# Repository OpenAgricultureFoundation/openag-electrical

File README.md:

# OpenAg Body
Body of electrical hardware to go with the brain software.
Electrical design based in Eagle. Mechanical design based in Solidworks.

*WORK IN PROGRESS*

## Electrical Design
### Setup
- Clone openag-body repo
- Point eagle program directories at corresponding openag-body repo

### Projects
- Create project directory structure
- Follow naming conventions
- Use standard docframe
- Add design blocks on standard grid
- Connect design blocks

### Parts
- Create part in logical group
- Follow naming conventions
- Add description using Digikey scraper
- Add required attributes
- Add standard name, value, & orientation

### Design Blocks
- Build on standard grid
- Add standard artwork
- Add standard signal interface
- Follow naming conventions

### Manufacturing Files
- Run CAM processor job
- Run BOM generation script

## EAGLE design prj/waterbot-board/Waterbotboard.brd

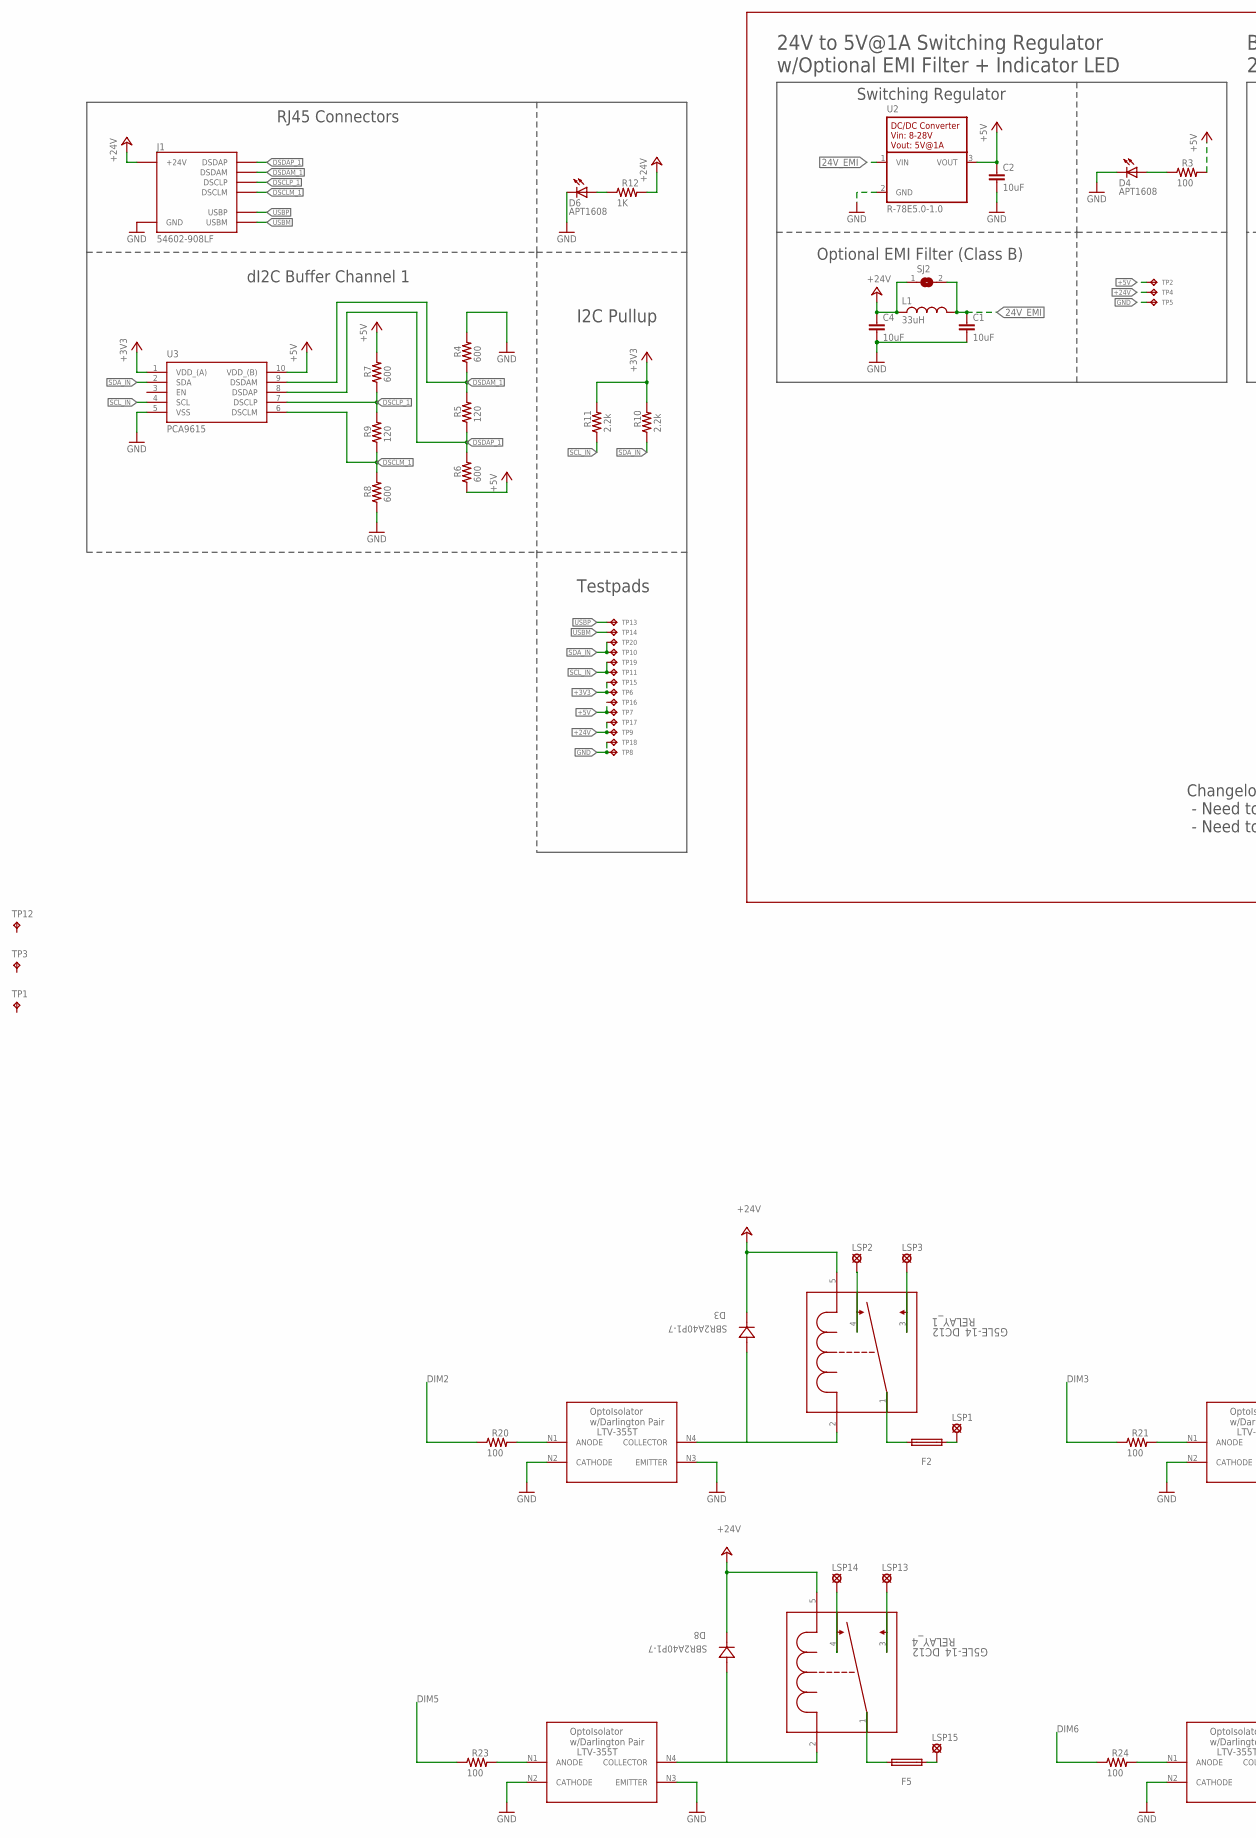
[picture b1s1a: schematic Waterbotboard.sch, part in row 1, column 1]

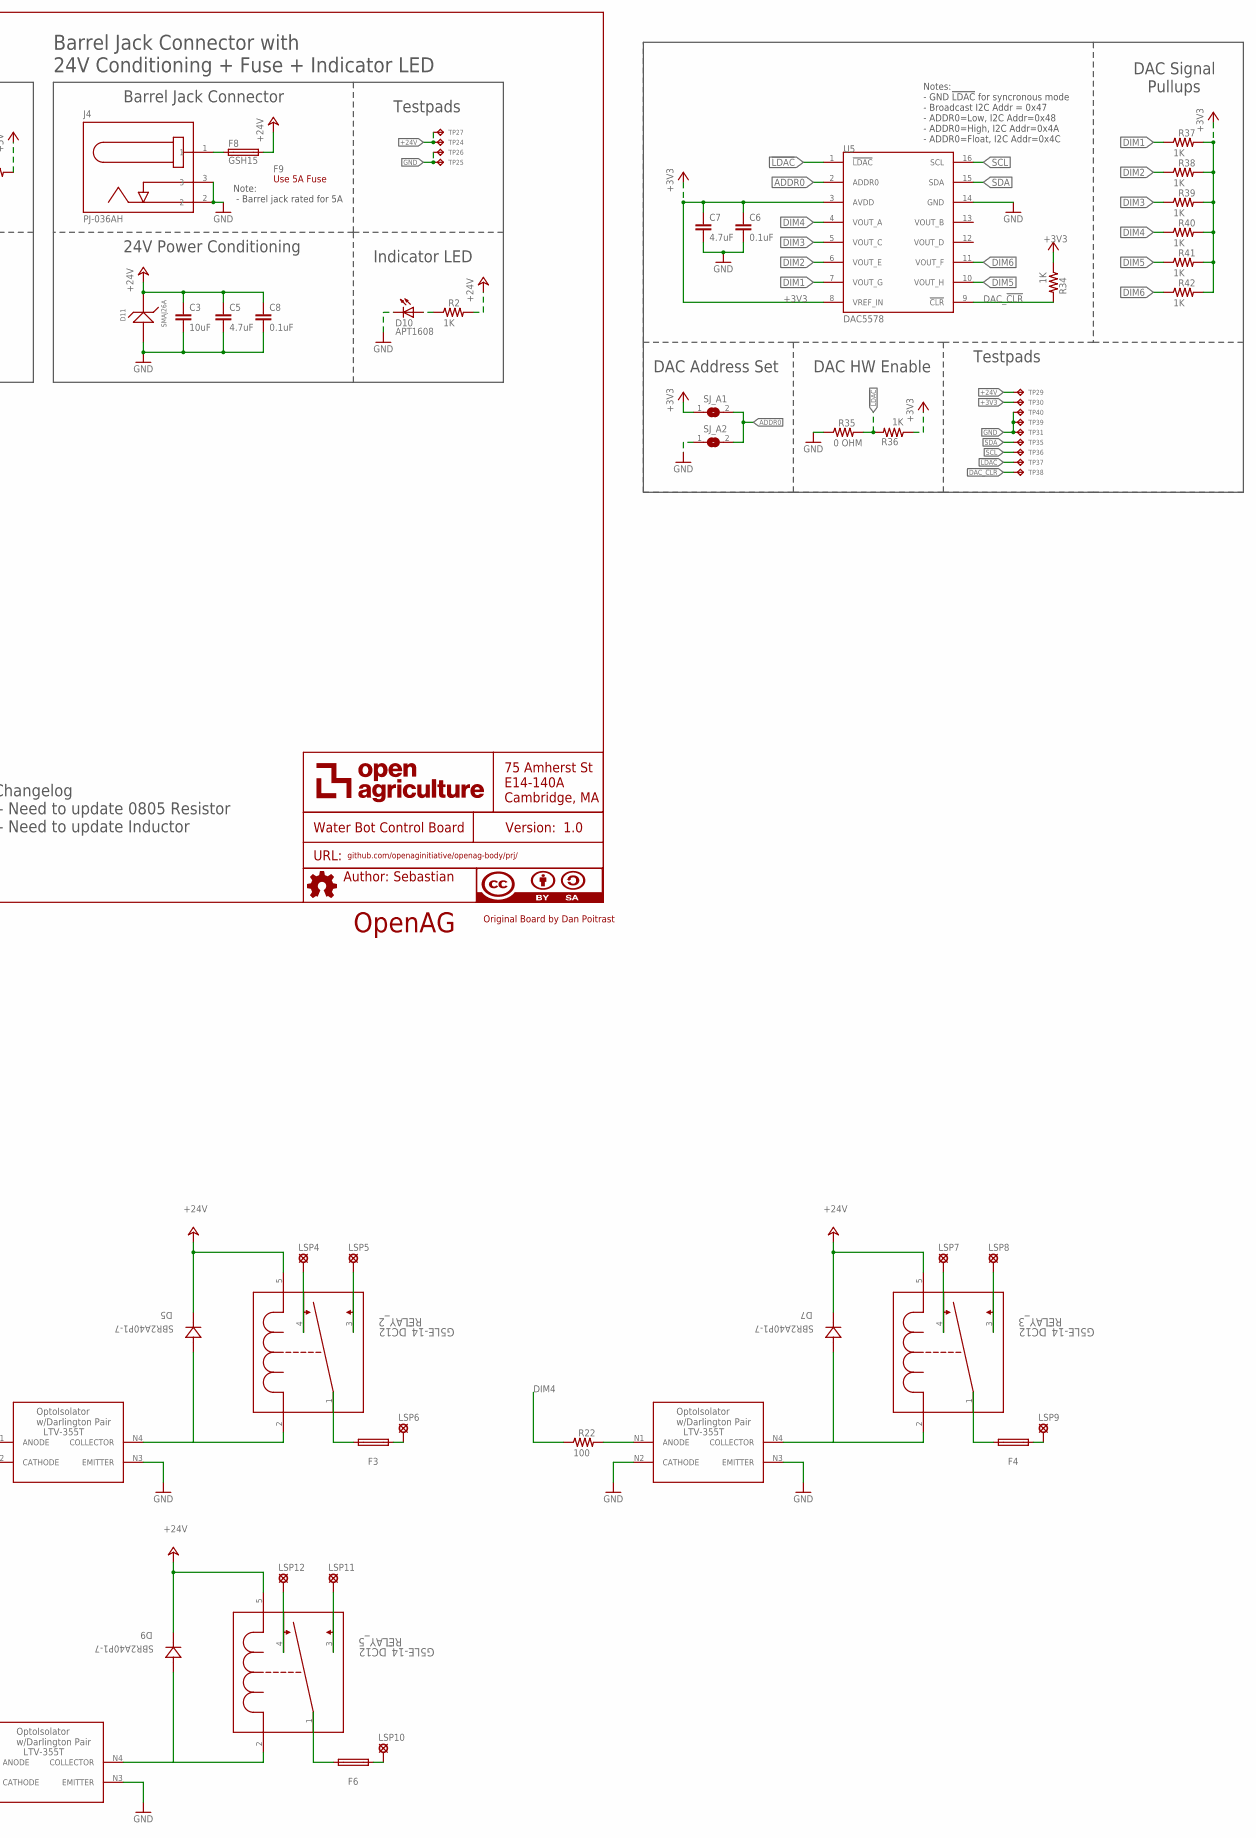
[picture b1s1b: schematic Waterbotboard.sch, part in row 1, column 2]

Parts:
C1, C2, C3, C4: 10uF; C0805
C5, C7: 4.7uF; C0805
C6, C8: 0.1uF; C0603
D3, D5, D7, D8, D9: SBR2A40P1-7; POWERDI123
D4, D6, D10: APT1608; CHIPLED_0603
D11: SMAJ26A; SMA
F2, F3, F4, F5, F6, F8: GSH15
F9: Use 5A Fuse; FUSE-CARTRIDGE
J1: 54602-908LF; RJ45-DI2C-USB-54602-908LF
J4: PJ-036AH; BARREL-JACK-PJ-036AH
L1: 33uH; 29333C
LSP1, LSP2, LSP3, LSP4, LSP5, LSP6, LSP7, LSP8, LSP9, LSP10, LSP11, LSP12, LSP13, LSP14, LSP15: LSP13
R2, R12, R34, R36, R37, R38, R39, R40, R41, R42: 1K; RC0603N
R3, R20, R21, R22, R23, R24: 100; RC0603N
R4, R6, R7, R8: 600; RC0603N
R5, R9: 120; RC0603N
R10, R11: 2.2k; RC0603N
R35: 0 OHM; RC0603N
RELAY_1, RELAY_2, RELAY_3, RELAY_4, RELAY_5: G5LE-14_DC12; RELAY_G5LE-1
SJ2: EMI-BYPASS
SJ_A1, SJ_A2: SOLDERJUMPERREFLOW_NOPASTE; SJ1
TP1, TP3, TP12: TPB2,54; B2,54
TP2, TP4, TP5: TPTP06R; TP06R
TP6, TP7, TP8, TP9, TP10, TP11, TP13, TP14, TP15, TP16, TP17, TP18, TP19, TP20, TP24, TP25, TP26, TP27, TP29, TP30, TP31, TP35, TP36, TP37, TP38, TP39, TP40: TPTP04R; TP04R
U2: R-78E5.0-1.0
U3: PCA9615; SOP50P490X110-10N
U5: DAC5578; TSSOP16
U$6: AUTHOR
U$7: TITLE
U$10, U$11, U$12, U$13, U$14: LTV-355T

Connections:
24V_EMI: C1.1, L1.2, SJ2.2, U2.1 (VIN)
24V_IN1: F8.1, J4.1
!LDAC!: R35.2, R36.2, TP37.1, U5.1 (!LDAC!)
+3V3: C6.1, C7.1, R10.2, R11.2, R34.1, R36.1, R37.2, R38.2, R39.2, R40.2, R41.2, R42.2, SJ_A1.1, TP6.1, TP15.1, TP30.1, U3.1 (VDD_(A)), U5.3 (AVDD), U5.8 (VREF_IN)
+5V: C2.1, R3.2, R6.1, R7.2, TP2.TP, TP7.1, TP16.1, U2.3 (VOUT), U3.10 (VDD_(B))
+24V: C3.1, C4.1, C5.1, C8.1, D3.-, D5.-, D7.-, D8.-, D9.-, D11.1, F8.2, J1.24V(6) (+24V), L1.1, R2.2, R12.2, RELAY_1.5, RELAY_2.5, RELAY_3.5, RELAY_4.5, RELAY_5.5, SJ2.1, TP4.TP, TP9.1, TP17.1, TP24.1, TP27.1, TP29.1
ADDR0: SJ_A1.2, SJ_A2.2, U5.2 (ADDR0)
DAC_!CLR!: R34.2, TP38.1, U5.9 (!CLR!)
DIM1: R37.1, U5.7 (VOUT_G)
DIM2: R20.1, R38.1, U5.6 (VOUT_E)
DIM3: R21.1, R39.1, U5.5 (VOUT_C)
DIM4: R22.1, R40.1, U5.4 (VOUT_A)
DIM5: R23.1, R41.1, U5.10 (VOUT_H)
DIM6: R24.1, R42.1, U5.11 (VOUT_F)
DSCLM_1: J1.DSCLM(5) (DSCLM), R8.2, R9.1, U3.6 (DSCLM)
DSCLP_1: J1.DSCLP(4) (DSCLP), R7.1, R9.2, U3.7 (DSCLP)
DSDAM_1: J1.DSDAM(2) (DSDAM), R4.1, R5.2, U3.9 (DSDAM)
DSDAP_1: J1.DSDAP(1) (DSDAP), R5.1, R6.2, U3.8 (DSDAP)
GND: C1.2, C2.2, C3.2, C4.2, C5.2, C6.2, C7.2, C8.2, D4.C, D6.C, D10.C, D11.2, J1.GND(3) (GND), J4.2, J4.3, R4.2, R8.1, R35.1, SJ_A2.1, TP5.TP, TP8.1, TP18.1, TP25.1, TP26.1, TP31.1, TP39.1, TP40.1, U2.2 (GND), U3.5 (VSS), U5.14 (GND), U$10.N2 (CATHODE), U$10.N3 (EMITTER), U$11.N2 (CATHODE), U$11.N3 (EMITTER), U$12.N2 (CATHODE), U$12.N3 (EMITTER), U$13.N2 (CATHODE), U$13.N3 (EMITTER), U$14.N2 (CATHODE), U$14.N3 (EMITTER)
unnamed: F2.1, LSP1.MP
unnamed: F5.1, LSP15.MP
unnamed: F6.1, LSP10.MP
unnamed: F3.1, LSP6.MP
unnamed: F4.1, LSP9.MP
unnamed: LSP2.MP, RELAY_1.4
unnamed: LSP4.MP, RELAY_2.4
unnamed: LSP7.MP, RELAY_3.4
unnamed: D4.A, R3.1
unnamed: D3.+, RELAY_1.2 (1), U$10.N4 (COLLECTOR)
unnamed: D6.A, R12.1
unnamed: F2.2, RELAY_1.1 (2)
unnamed: LSP3.MP, RELAY_1.3
unnamed: LSP12.MP, RELAY_5.4
unnamed: R20.2, U$10.N1 (ANODE)
unnamed: D5.+, RELAY_2.2 (1), U$11.N4 (COLLECTOR)
unnamed: F3.2, RELAY_2.1 (2)
unnamed: LSP5.MP, RELAY_2.3
unnamed: LSP14.MP, RELAY_4.4
unnamed: R21.2, U$11.N1 (ANODE)
unnamed: D7.+, RELAY_3.2 (1), U$12.N4 (COLLECTOR)
unnamed: F4.2, RELAY_3.1 (2)
unnamed: LSP8.MP, RELAY_3.3
unnamed: R22.2, U$12.N1 (ANODE)
unnamed: D8.+, RELAY_4.2 (1), U$13.N4 (COLLECTOR)
unnamed: F5.2, RELAY_4.1 (2)
unnamed: LSP13.MP, RELAY_4.3
unnamed: D10.A, R2.1
unnamed: R23.2, U$13.N1 (ANODE)
unnamed: D9.+, RELAY_5.2 (1), U$14.N4 (COLLECTOR)
unnamed: F6.2, RELAY_5.1 (2)
unnamed: LSP11.MP, RELAY_5.3
unnamed: R24.2, U$14.N1 (ANODE)
SCL: TP36.1, U5.16 (SCL)
SCL_IN: R11.1, TP11.1, TP19.1, U3.4 (SCL)
SDA: TP35.1, U5.15 (SDA)
SDA_IN: R10.1, TP10.1, TP20.1, U3.2 (SDA)
USBM: J1.USBM(8) (USBM), TP14.1
USBP: J1.USBP(7) (USBP), TP13.1

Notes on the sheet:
Changelog - Need to update 0805 Resistor - Need to update Inductor
OpenAG
Original Board by Dan Poitrast
24V to 5V@1A Switching Regulator w/Optional EMI Filter + Indicator LED
Switching Regulator
Optional EMI Filter (Class B)
dI2C Buffer Channel 1
RJ45 Connectors
Testpads
I2C Pullup
LTV-355T
Notes: - GND !LDAC! for syncronous mode - Broadcast I2C Addr = 0x47 - ADDR0=Low, I2C Addr=0x48 - ADDR0=High, I2C Addr=0x4A - ADDR0=Float, I2C Addr=0x4C
DAC Signal Pullups
DAC Address Set
DAC HW Enable
Barrel Jack Connector
Barrel Jack Connector with 24V Conditioning + Fuse + Indicator LED
24V Power Conditioning
Indicator LED
Note: - Barrel jack rated for 5A

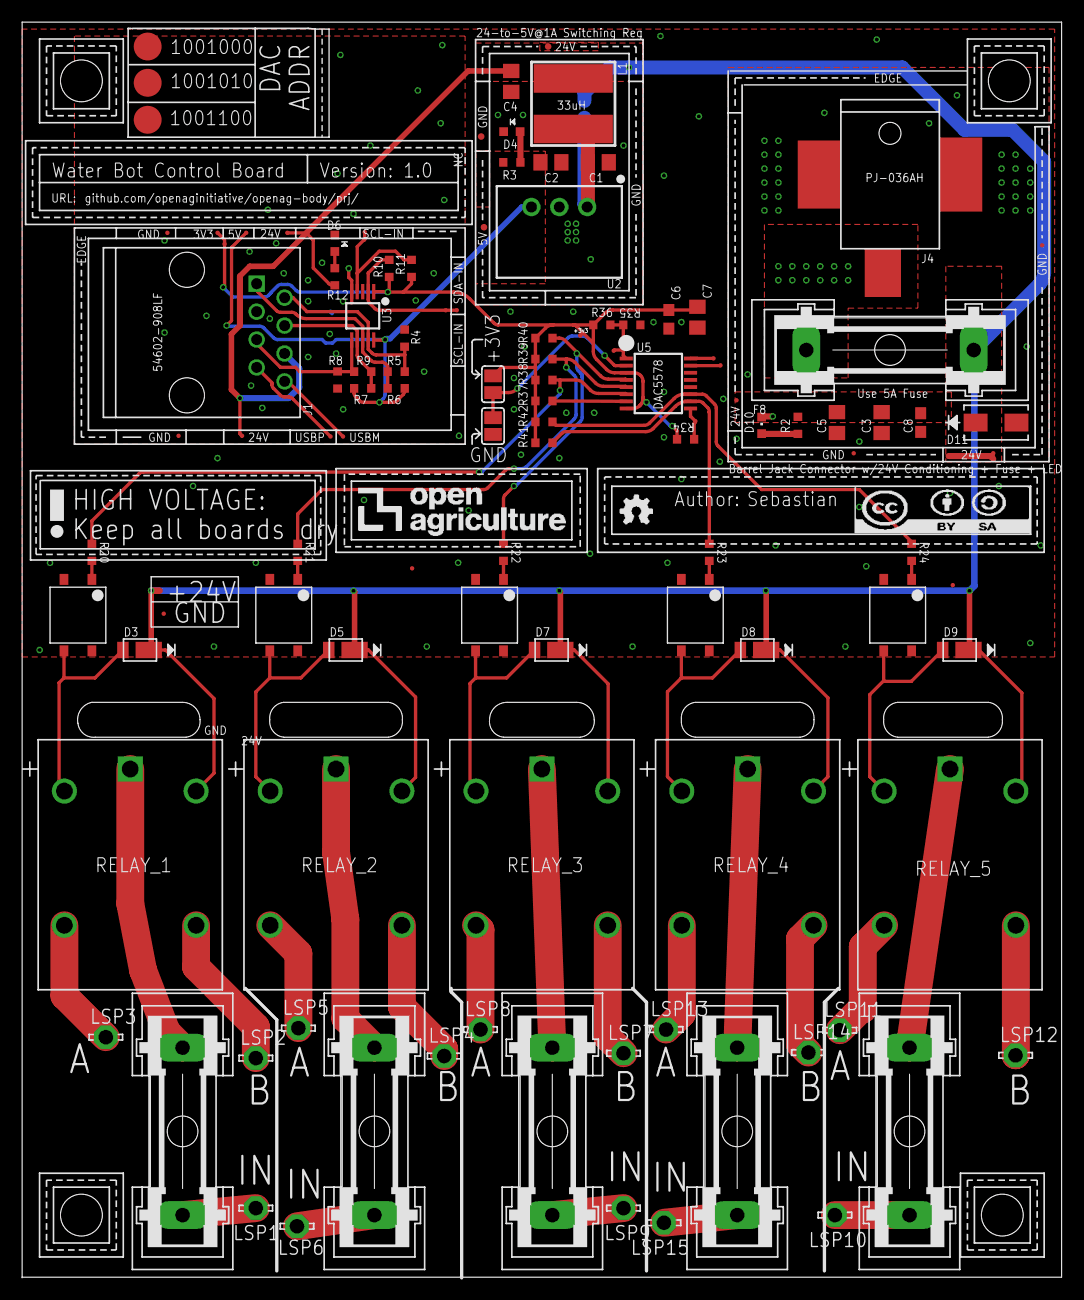
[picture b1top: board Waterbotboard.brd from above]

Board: 2 copper layers, 94.6 x 114.3 mm, 123 parts (1 on the bottom side), 58 nets.

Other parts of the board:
U$1, U$2, U$3, U$4: CORNER
U$5: LOGO

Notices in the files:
parts and their libraries:
SparkFun-Resistors: Licensing: Creative Commons ShareAlike 4.0 International - https://creativecommons.org/licenses/by-sa/4.0
SparkFun-Aesthetics: Licensing: CC v3.0 Share-Alike You are welcome to use this library for commercial purposes.
